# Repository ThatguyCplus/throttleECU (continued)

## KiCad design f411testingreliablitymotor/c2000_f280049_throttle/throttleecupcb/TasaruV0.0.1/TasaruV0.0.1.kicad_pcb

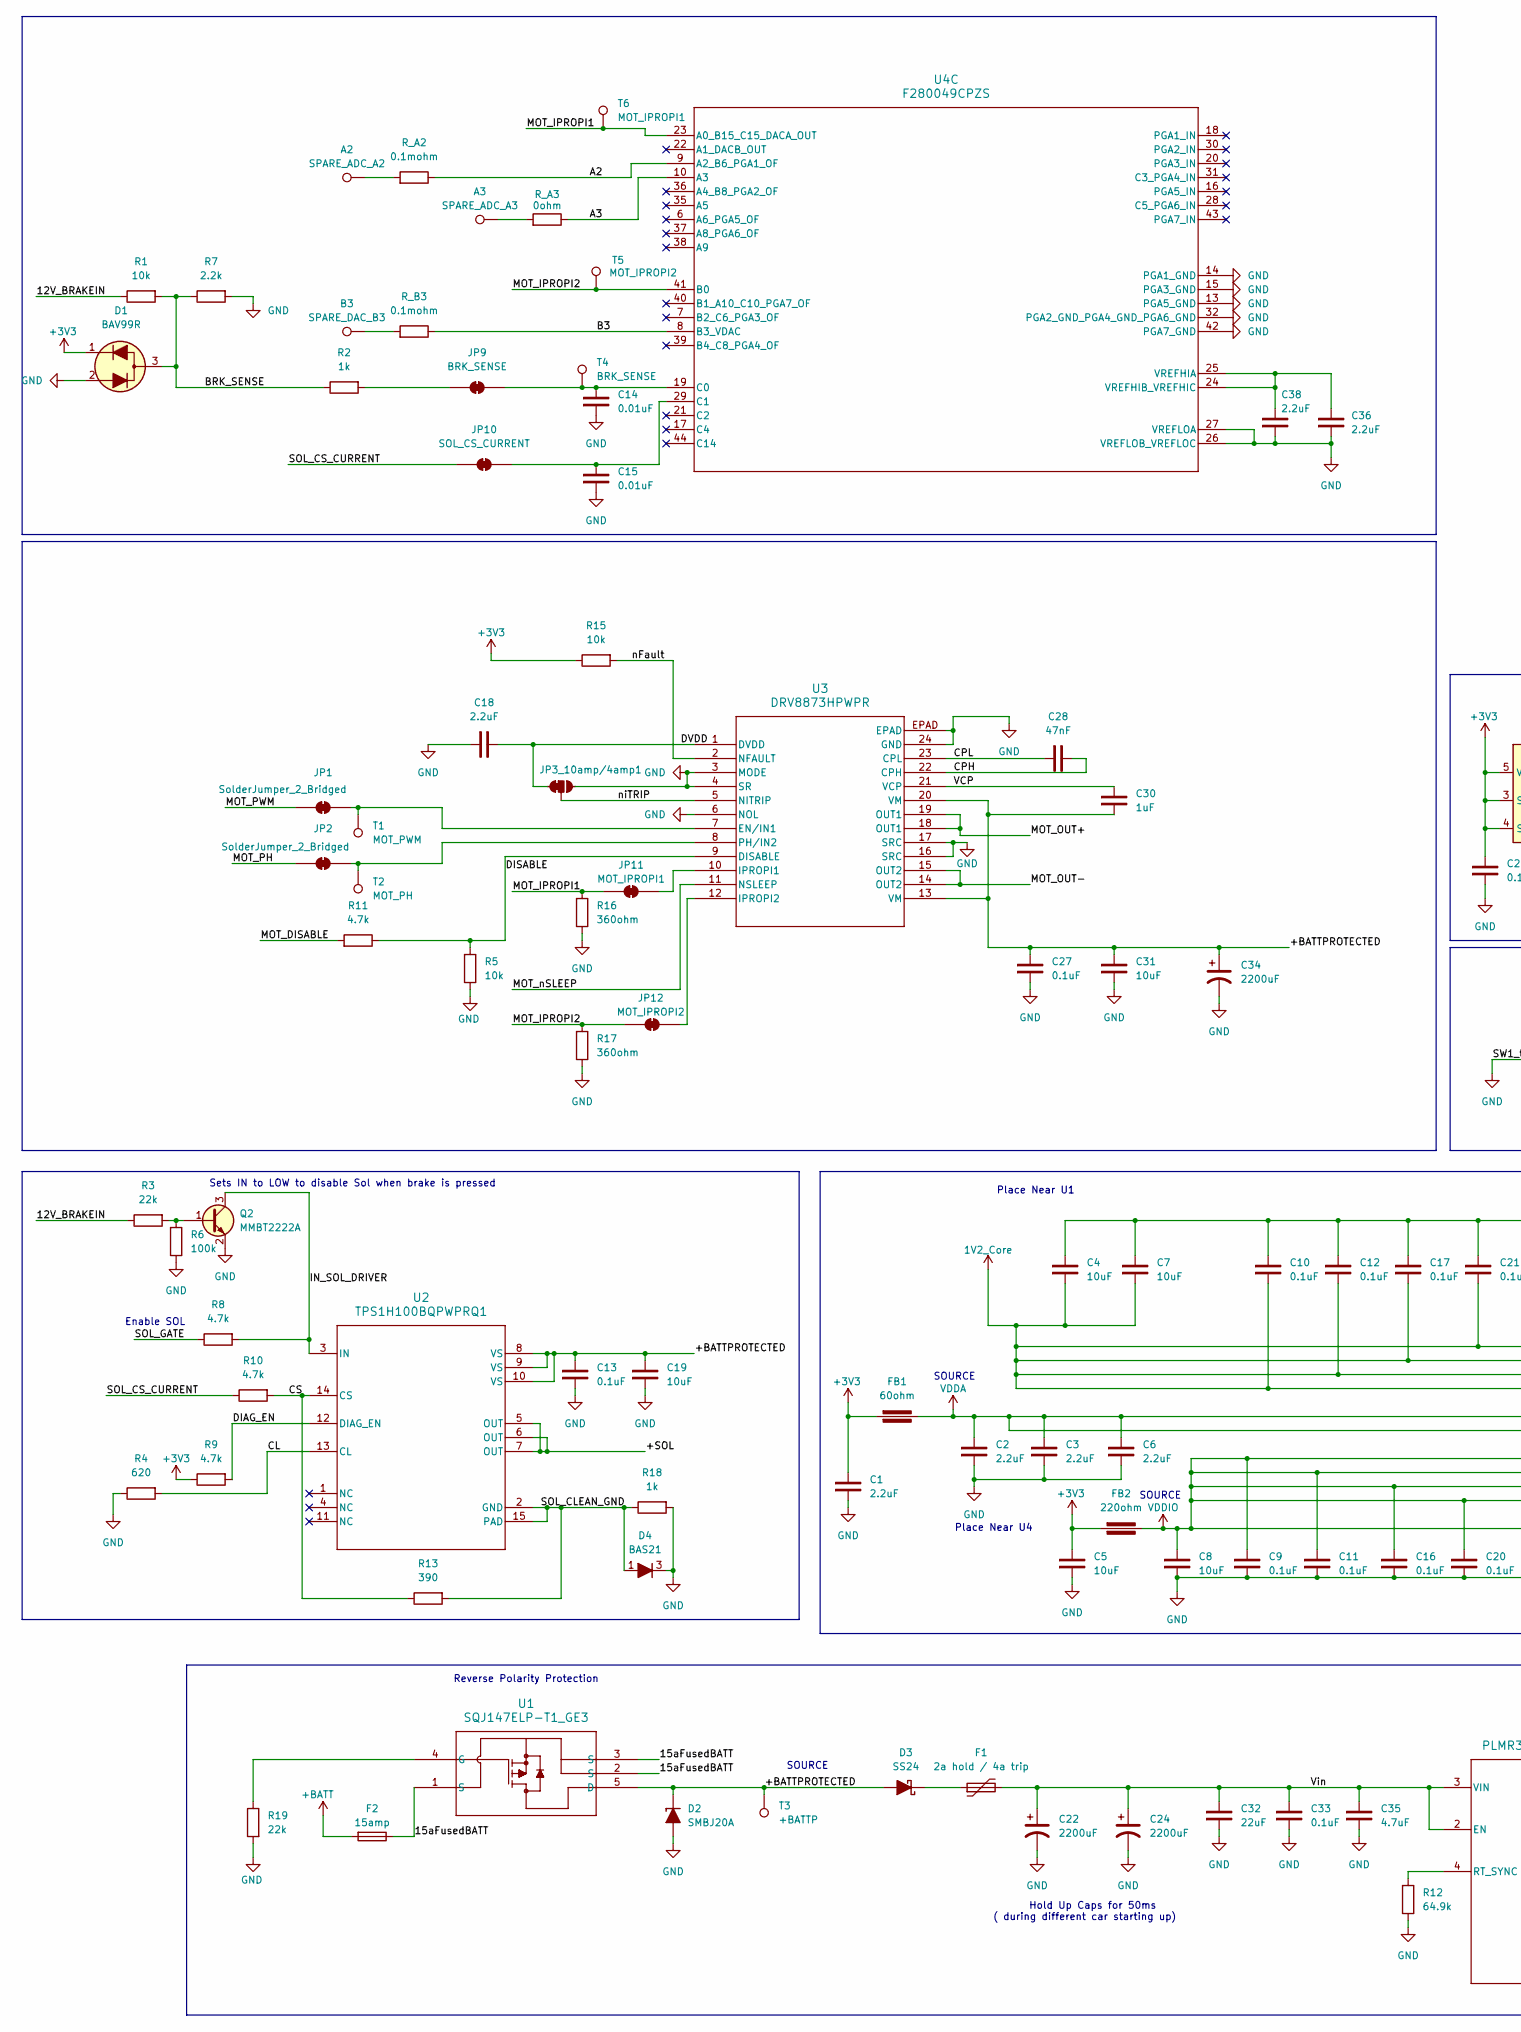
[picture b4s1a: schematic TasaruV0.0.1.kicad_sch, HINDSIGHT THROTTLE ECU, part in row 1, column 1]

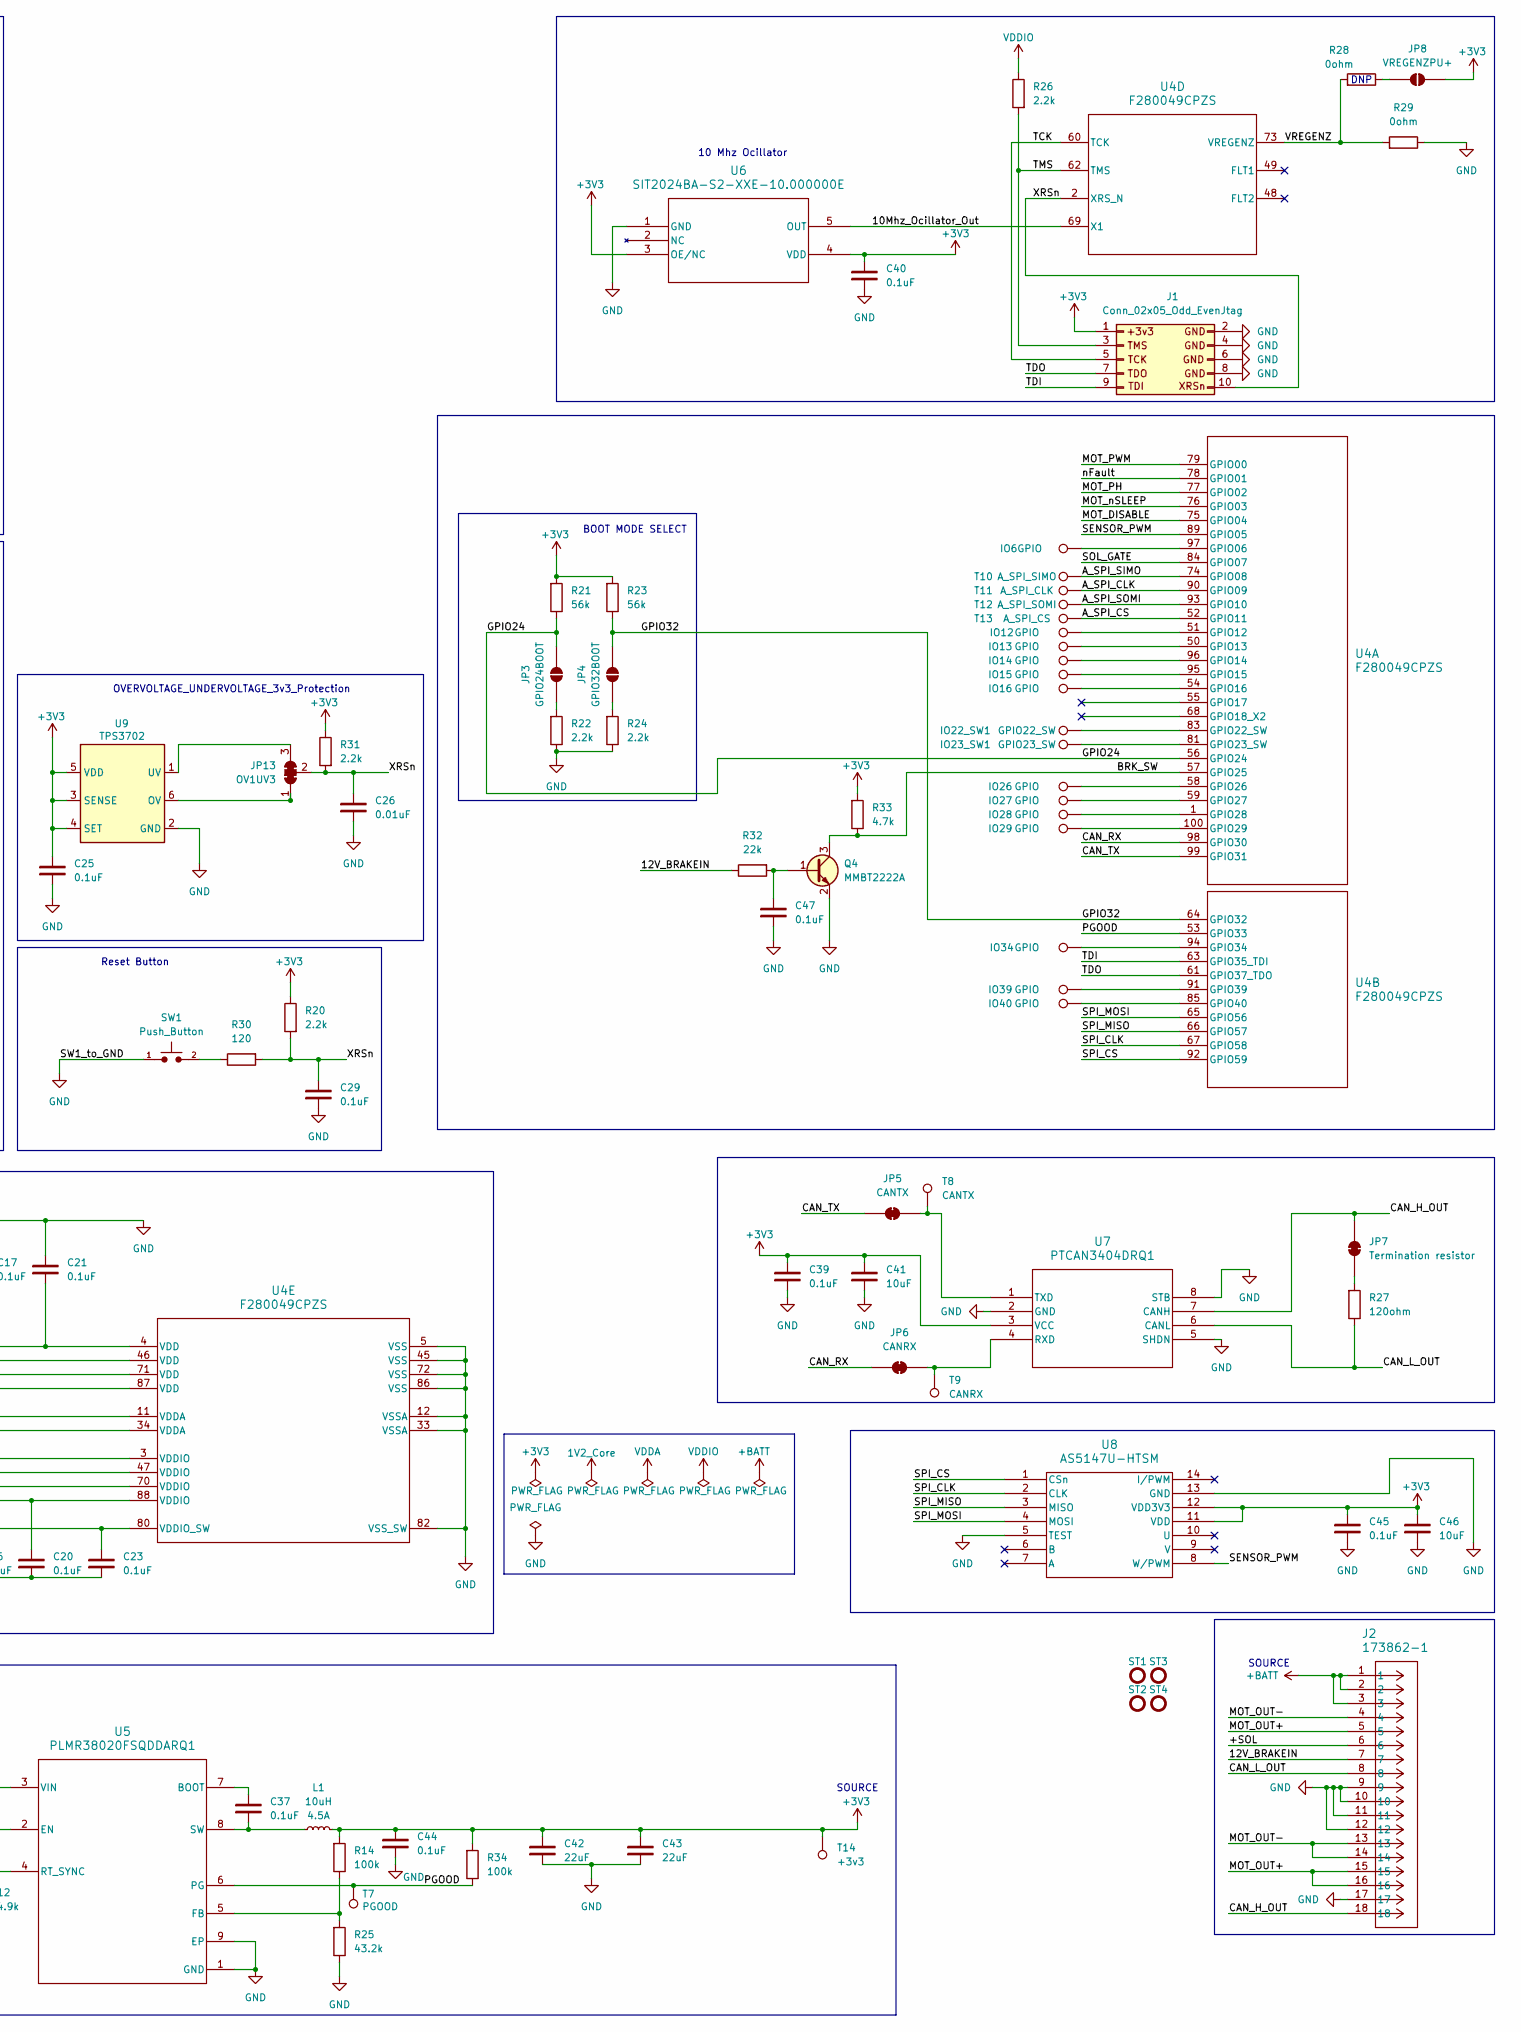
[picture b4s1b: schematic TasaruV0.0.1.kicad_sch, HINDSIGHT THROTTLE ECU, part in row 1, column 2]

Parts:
A2: SPARE_ADC_A2; TestPoint_Pad_D1.5mm
A3: SPARE_ADC_A3; TestPoint_Pad_D1.5mm
B3: SPARE_DAC_B3; TestPoint_Pad_D1.5mm
C1, C2, C3, C6, C18, C36, C38: 2.2uF; C_0603_1608Metric_Pad1.08x0.95mm_HandSolder
C4, C5, C7, C8, C19, C31, C41, C46: 10uF; C_0805_2012Metric_Pad1.18x1.45mm_HandSolder
C9, C10, C11, C12, C13, C16, C17, C20, C21, C23, C25, C27, C29, C37, C39, C40, C44, C45, C47: 0.1uF; C_0603_1608Metric_Pad1.08x0.95mm_HandSolder
C14, C15, C26: 0.01uF; C_0603_1608Metric_Pad1.08x0.95mm_HandSolder
C22, C24, C34: 2200uF; CP_Radial_D12.5mm_P5.00mm
C28: 47nF; C_0603_1608Metric_Pad1.08x0.95mm_HandSolder
C30: 1uF; C_0603_1608Metric_Pad1.08x0.95mm_HandSolder
C32, C42, C43: 22uF; C_1206_3216Metric_Pad1.33x1.80mm_HandSolder
C33: 0.1uF; C_1206_3216Metric_Pad1.33x1.80mm_HandSolder
C35: 4.7uF; C_0603_1608Metric_Pad1.08x0.95mm_HandSolder
D1: BAV99R; SOT-23
D2: SMBJ20A; D_SMB_TVS
D3: SS24; D_SMB
D4: BAS21; SOT-23_Handsoldering
F1: 2a hold / 4a trip; Fuse_1812_4532Metric_Pad1.30x3.40mm_HandSolder
F2: 15amp; Fuseholder_Blade_Mini_Keystone_3568
FB1: 60ohm; Fuse_0603_1608Metric_Pad1.05x0.95mm_HandSolder
FB2: 220ohm; Fuse_0603_1608Metric_Pad1.05x0.95mm_HandSolder
IO6, IO12, IO13, IO14, IO15, IO16, IO26, IO27, IO28, IO29, IO34, IO39, IO40: GPIO; TestPoint_Pad_D1.0mm
IO22_SW1: GPIO22_SW; TestPoint_Pad_D1.0mm
IO23_SW1: GPIO23_SW; TestPoint_Pad_D1.0mm
J1: Conn_02x05_Odd_EvenJtag; IDC-Header_2x05_P2.54mm_Vertical
J2: 173862-1; CONN_173862-1_TYC
JP1, JP2: SolderJumper_2_Bridged; SolderJumper-2_P1.3mm_Bridged2Bar_RoundedPad1.0x1.5mm
JP3: GPIO24BOOT; SolderJumper-2_P1.3mm_Open_RoundedPad1.0x1.5mm
JP3_10amp/4amp1: SolderJumper-3_P1.3mm_Bridged12_RoundedPad1.0x1.5mm_NumberL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
JP4: GPIO32BOOT; SolderJumper-2_P1.3mm_Open_RoundedPad1.0x1.5mm
JP5: CANTX; SolderJumper-2_P1.3mm_Bridged2Bar_RoundedPad1.0x1.5mm
JP6: CANRX; SolderJumper-2_P1.3mm_Bridged2Bar_RoundedPad1.0x1.5mm
JP7: Termination resistor; SolderJumper-2_P1.3mm_Bridged2Bar_RoundedPad1.0x1.5mm
JP8: VREGENZPU+; SolderJumper-2_P1.3mm_Open_RoundedPad1.0x1.5mm
JP9: BRK_SENSE; SolderJumper-2_P1.3mm_Bridged2Bar_RoundedPad1.0x1.5mm
JP10: SOL_CS_CURRENT; SolderJumper-2_P1.3mm_Bridged2Bar_RoundedPad1.0x1.5mm
JP11: MOT_IPROPI1; SolderJumper-2_P1.3mm_Bridged2Bar_RoundedPad1.0x1.5mm
JP12: MOT_IPROPI2; SolderJumper-2_P1.3mm_Bridged2Bar_RoundedPad1.0x1.5mm
JP13: OV1UV3; SolderJumper-3_P1.3mm_Bridged123_RoundedPad1.0x1.5mm_Number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
L1: 10uH; Inductor_7.3x6.6mm
Q2, Q4: MMBT2222A; SOT-23
R1, R5, R15: 10k; R_0402_1005Metric_Pad0.72x0.64mm_HandSolder
R2, R18: 1k; R_0402_1005Metric_Pad0.72x0.64mm_HandSolder
R3, R32: 22k; R_0402_1005Metric_Pad0.72x0.64mm_HandSolder
R4: 620; R_0402_1005Metric_Pad0.72x0.64mm_HandSolder
R6, R14: 100k; R_0402_1005Metric_Pad0.72x0.64mm_HandSolder
R7, R20, R22, R24, R26, R31: 2.2k; R_0402_1005Metric_Pad0.72x0.64mm_HandSolder
R8, R9, R10, R11, R33: 4.7k; R_0402_1005Metric_Pad0.72x0.64mm_HandSolder
R12: 64.9k; R_0402_1005Metric_Pad0.72x0.64mm_HandSolder
R13: 390; R_0402_1005Metric_Pad0.72x0.64mm_HandSolder
R16, R17: 360ohm; R_0603_1608Metric_Pad0.98x0.95mm_HandSolder
R19: 22k; R_0603_1608Metric_Pad0.98x0.95mm_HandSolder
R21, R23: 56k; R_0402_1005Metric_Pad0.72x0.64mm_HandSolder
R25: 43.2k; R_0603_1608Metric_Pad0.98x0.95mm_HandSolder
R27: 120ohm; R_0603_1608Metric_Pad0.98x0.95mm_HandSolder
R28, R29: 0ohm; R_0402_1005Metric_Pad0.72x0.64mm_HandSolder
R30: 120; R_0603_1608Metric_Pad0.98x0.95mm_HandSolder
R34: 100k; R_0603_1608Metric_Pad0.98x0.95mm_HandSolder
R_A2: 0.1mohm; R_0402_1005Metric_Pad0.72x0.64mm_HandSolder
R_A3: 0ohm; R_0402_1005Metric_Pad0.72x0.64mm_HandSolder
R_B3: 0.1mohm; R_0402_1005Metric_Pad0.72x0.64mm_HandSolder
ST1, ST2, ST3, ST4: FASTNER; Standoff_Hole-2.75mm_Clearance-1.625mm
SW1: Push_Button; SW_PUSH_6mm_H5mm
T1: MOT_PWM; TestPoint_Pad_D1.0mm
T2: MOT_PH; TestPoint_Pad_D1.0mm
T3: +BATTP; TestPoint_Pad_D1.0mm
T4: BRK_SENSE; TestPoint_Pad_D1.0mm
T5: MOT_IPROPI2; TestPoint_Pad_D1.0mm
T6: MOT_IPROPI1; TestPoint_Pad_D1.0mm
T7: PGOOD; TestPoint_Pad_D1.0mm
T8: CANTX; TestPoint_Pad_D1.0mm
T9: CANRX; TestPoint_Pad_D1.0mm
T10: A_SPI_SIMO; TestPoint_Pad_D1.0mm
T11: A_SPI_CLK; TestPoint_Pad_D1.0mm
T12: A_SPI_SOMI; TestPoint_Pad_D1.0mm
T13: A_SPI_CS; TestPoint_Pad_D1.0mm
T14: +3v3; TestPoint_Pad_D1.0mm
U1: SQJ147ELP-T1_GE3; PowerPAK_SO-8L_3_VIS
U2: TPS1H100BQPWPRQ1; PWP0014F_M
U3: DRV8873HPWPR; PWP24_TEX-M
U4: F280049CPZS; PZ0100A_M
U5: PLMR38020FSQDDARQ1; DDA0008E-IPC_A
U6: SIT2024BA-S2-XXE-10.000000E; SOT_SiT1630-S_SIT
U7: PTCAN3404DRQ1; SOIC8_D_TEX-M
U8: AS5147U-HTSM; TSSOP14_AMS-M
U9: TPS3702; SOT-23-6_Handsoldering

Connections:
1V2_Core: C4.1, C7.1, C10.1, C12.1, C17.1, C21.1, U4.4 (VDD), U4.46 (VDD), U4.71 (VDD), U4.87 (VDD)
+3V3: C1.2, C5.2, C25.2, C39.2, C40.2, C41.2, C42.2, C43.2, C44.2, C45.2, C46.2, D1.1 (A), FB1.1, FB2.1, J1.1, JP8.2 (B), L1.2, R9.2, R14.1, R15.2, R20.2, R21.1, R23.1, R31.2, R33.1, R34.1, T14.1 (1_1), U6.3 (OE/NC), U6.4 (VDD), U7.3 (VCC), U8.11 (VDD), U8.12 (VDD3V3), U9.3 (SENSE), U9.4 (SET), U9.5 (VDD)
+BATT: F2.2, J2.1, J2.2, J2.3
/10Mhz_Ocillator_Out: U4.69 (X1), U6.5 (OUT)
/12V_BRAKEIN: J2.7, R1.2, R3.2, R32.2
/15aFusedBATT: F2.1, U1.1 (S), U1.2 (S), U1.3 (S)
/+BATTPROTECTED: C13.2, C19.2, C27.2, C30.1, C31.2, C34.1, D2.1 (K), D3.2 (A), T3.1 (1_1), U1.5 (D), U2.8 (VS), U2.9 (VS), U2.10 (VS), U3.13 (VM), U3.20 (VM)
/+SOL: J2.6, U2.5 (OUT), U2.6 (OUT), U2.7 (OUT)
/A2: R_A2.2, U4.9 (A2_B6_PGA1_OF)
/A3: R_A3.2, U4.10 (A3)
/A_SPI_CLK: T11.1 (1_1), U4.90 (GPIO09)
/A_SPI_CS: T13.1 (1_1), U4.52 (GPIO11)
/A_SPI_SIMO: T10.1 (1_1), U4.74 (GPIO08)
/A_SPI_SOMI: T12.1 (1_1), U4.93 (GPIO10)
/B3: R_B3.2, U4.8 (B3_VDAC)
/BRK_SENSE: D1.3 (C), R1.1, R2.2, R7.2
/BRK_SW: Q4.3 (C), R33.2, U4.57 (GPIO25)
/CAN_H_OUT: J2.18, JP7.2 (B), U7.7 (CANH)
/CAN_L_OUT: J2.8, R27.2, U7.6 (CANL)
/CAN_RX: JP6.1 (A), U4.98 (GPIO30)
/CAN_TX: JP5.1 (A), U4.99 (GPIO31)
/CL: R4.1, U2.13 (CL)
/CPH: C28.2, U3.22 (CPH)
/CPL: C28.1, U3.23 (CPL)
/CS: R10.1, R13.2, U2.14 (CS)
/DIAG_EN: R9.1, U2.12 (DIAG_EN)
/DISABLE: R5.1, R11.2, U3.9 (DISABLE)
/DVDD: C18.2, JP3_10amp/4amp1.1 (A), U3.1 (DVDD)
/GPIO24: JP3.2 (B), R21.2, U4.56 (GPIO24)
/GPIO32: JP4.2 (B), R23.2, U4.64 (GPIO32)
/IN_SOL_DRIVER: Q2.3 (C), R8.1, U2.3 (IN)
/MOT_DISABLE: R11.1, U4.75 (GPIO04)
/MOT_IPROPI1: JP11.1 (A), R16.1, T6.1 (1_1), U4.23 (A0_B15_C15_DACA_OUT)
/MOT_IPROPI2: JP12.1 (A), R17.1, T5.1 (1_1), U4.41 (B0)
/MOT_OUT+: J2.5, J2.15, J2.16, U3.18 (OUT1), U3.19 (OUT1)
/MOT_OUT-: J2.4, J2.13, J2.14, U3.14 (OUT2), U3.15 (OUT2)
/MOT_PH: JP2.1 (A), U4.77 (GPIO02)
/MOT_PWM: JP1.1 (A), U4.79 (GPIO00)
/MOT_nSLEEP: U3.11 (NSLEEP), U4.76 (GPIO03)
/PGOOD: R34.2, T7.1 (1_1), U4.53 (GPIO33), U5.6 (PG)
/SENSOR_PWM: U4.89 (GPIO05), U8.8 (W/PWM)
/SOL_CLEAN_GND: D4.1 (A), R13.1, R18.2, U2.2 (GND), U2.15 (PAD)
/SOL_CS_CURRENT: JP10.1 (A), R10.2
/SOL_GATE: R8.2, U4.84 (GPIO07)
/SPI_CLK: U4.67 (GPIO58), U8.2 (CLK)
/SPI_CS: U4.92 (GPIO59), U8.1 (CSn)
/SPI_MISO: U4.66 (GPIO57), U8.3 (MISO)
/SPI_MOSI: U4.65 (GPIO56), U8.4 (MOSI)
/TCK: J1.5, U4.60 (TCK)
/TDI: J1.9, U4.63 (GPIO35_TDI)
/TDO: J1.7, U4.61 (GPIO37_TDO)
/TMS: J1.3, R26.1, U4.62 (TMS)
/VCP: C30.2, U3.21 (VCP)
/VREGENZ: R28.1, R29.1, U4.73 (VREGENZ)
/Vin: C22.1, C24.1, C32.2, C33.2, C35.2, F1.2, U5.2 (EN), U5.3 (VIN)
/XRSn: C26.2, C29.2, J1.10, JP13.2 (C), R20.1, R30.1, R31.1, U4.2 (XRS_N)
/nFault: R15.1, U3.2 (NFAULT), U4.78 (GPIO01)
/niTRIP: JP3_10amp/4amp1.2 (B), U3.5 (NITRIP)
GND: C1.1, C2.1, C3.1, C4.2, C5.1, C6.1, C7.2, C8.1, C9.1, C10.2, C11.1, C12.2, C13.1, C14.1, C15.1, C16.1, C17.2, C18.1, C19.1, C20.1, C21.2, C22.2, C23.1, C24.2, C25.1, C26.1, C27.1, C29.1, C31.1, C32.1, C33.1, C34.2, C35.1, C36.1, C38.1, C39.1, C40.1, C41.1, C42.1, C43.1, C44.1, C45.1, C46.1, C47.1, D1.2 (K), D2.2 (A), D4.3 (K), J1.2, J1.4, J1.6, J1.8, J2.9, J2.10, J2.11, J2.12, J2.17, JP3_10amp/4amp1.3 (C), Q2.2 (E), Q4.2 (E), R4.2, R5.2, R6.2, R7.1, R12.2, R16.2, R17.2, R18.1, R19.1, R22.2, R24.2, R25.2, R29.2, SW1.1, U3.3 (MODE), U3.4 (SR), U3.6 (NOL), U3.16 (SRC), U3.17 (SRC), U3.24 (GND), U3.EPAD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
unnamed: A2.1 (1_1), R_A2.1
unnamed: A3.1 (1_1), R_A3.1
unnamed: B3.1 (1_1), R_B3.1
unnamed: D3.1 (K), F1.1
unnamed: JP1.2 (B), T1.1 (1_1), U3.7 (EN/IN1)
unnamed: JP2.2 (B), T2.1 (1_1), U3.8 (PH/IN2)
unnamed: JP3.1 (A), R22.1
unnamed: JP4.1 (A), R24.1
unnamed: JP5.2 (B), T8.1 (1_1), U7.1 (TXD)
unnamed: JP6.2 (B), T9.1 (1_1), U7.4 (RXD)
unnamed: JP7.1 (A), R27.1
unnamed: JP8.1 (A), R28.2
unnamed: JP9.1 (A), R2.1
unnamed: C14.2, JP9.2 (B), T4.1 (1_1), U4.19 (C0)
unnamed: C15.2, JP10.2 (B), U4.29 (C1)
unnamed: JP11.2 (B), U3.10 (IPROPI1)
unnamed: JP12.2 (B), U3.12 (IPROPI2)
unnamed: JP13.1 (A), U9.6 (OV)
unnamed: JP13.3 (B), U9.1 (UV)
unnamed: Q2.1 (B), R3.1, R6.1
unnamed: C47.2, Q4.1 (B), R32.1
unnamed: R30.2, SW1.2
unnamed: R19.2, U1.4 (G)
unnamed: IO6.1 (1_1), U4.97 (GPIO06)
unnamed: IO12.1 (1_1), U4.51 (GPIO12)
unnamed: IO13.1 (1_1), U4.50 (GPIO13)
unnamed: IO14.1 (1_1), U4.96 (GPIO14)
unnamed: IO15.1 (1_1), U4.95 (GPIO15)
unnamed: IO16.1 (1_1), U4.54 (GPIO16)
unnamed: IO22_SW1.1 (1_1), U4.83 (GPIO22_SW)
unnamed: IO23_SW1.1 (1_1), U4.81 (GPIO23_SW)
unnamed: IO26.1 (1_1), U4.58 (GPIO26)
unnamed: IO27.1 (1_1), U4.59 (GPIO27)
unnamed: IO28.1 (1_1), U4.1 (GPIO28)
unnamed: IO29.1 (1_1), U4.100 (GPIO29)
unnamed: IO34.1 (1_1), U4.94 (GPIO34)
unnamed: IO39.1 (1_1), U4.91 (GPIO39)
unnamed: IO40.1 (1_1), U4.85 (GPIO40)
unnamed: C36.2, C38.2, U4.24 (VREFHIB_VREFHIC), U4.25 (VREFHIA)
unnamed: C37.2, U5.7 (BOOT)
unnamed: R14.2, R25.1, U5.5 (FB)
unnamed: R12.1, U5.4 (RT_SYNC)
unnamed: C37.1, L1.1, U5.8 (SW)
VDDA: C2.2, C3.2, C6.2, FB1.2, U4.11 (VDDA), U4.34 (VDDA)
VDDIO: C8.2, C9.2, C11.2, C16.2, C20.2, C23.2, FB2.2, R26.2, U4.3 (VDDIO), U4.47 (VDDIO), U4.70 (VDDIO), U4.80 (VDDIO_SW), U4.88 (VDDIO)

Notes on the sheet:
SOURCE
10 Mhz Ocillator
Sets IN to LOW to disable Sol when brake is pressed
DNP
Reverse Polarity Protection
BOOT MODE SELECT
OVERVOLTAGE_UNDERVOLTAGE_3v3_Protection
Hold Up Caps for 50ms ( during different car starting up)
Reset Button
Place Near U4
Enable SOL
Place Near U1

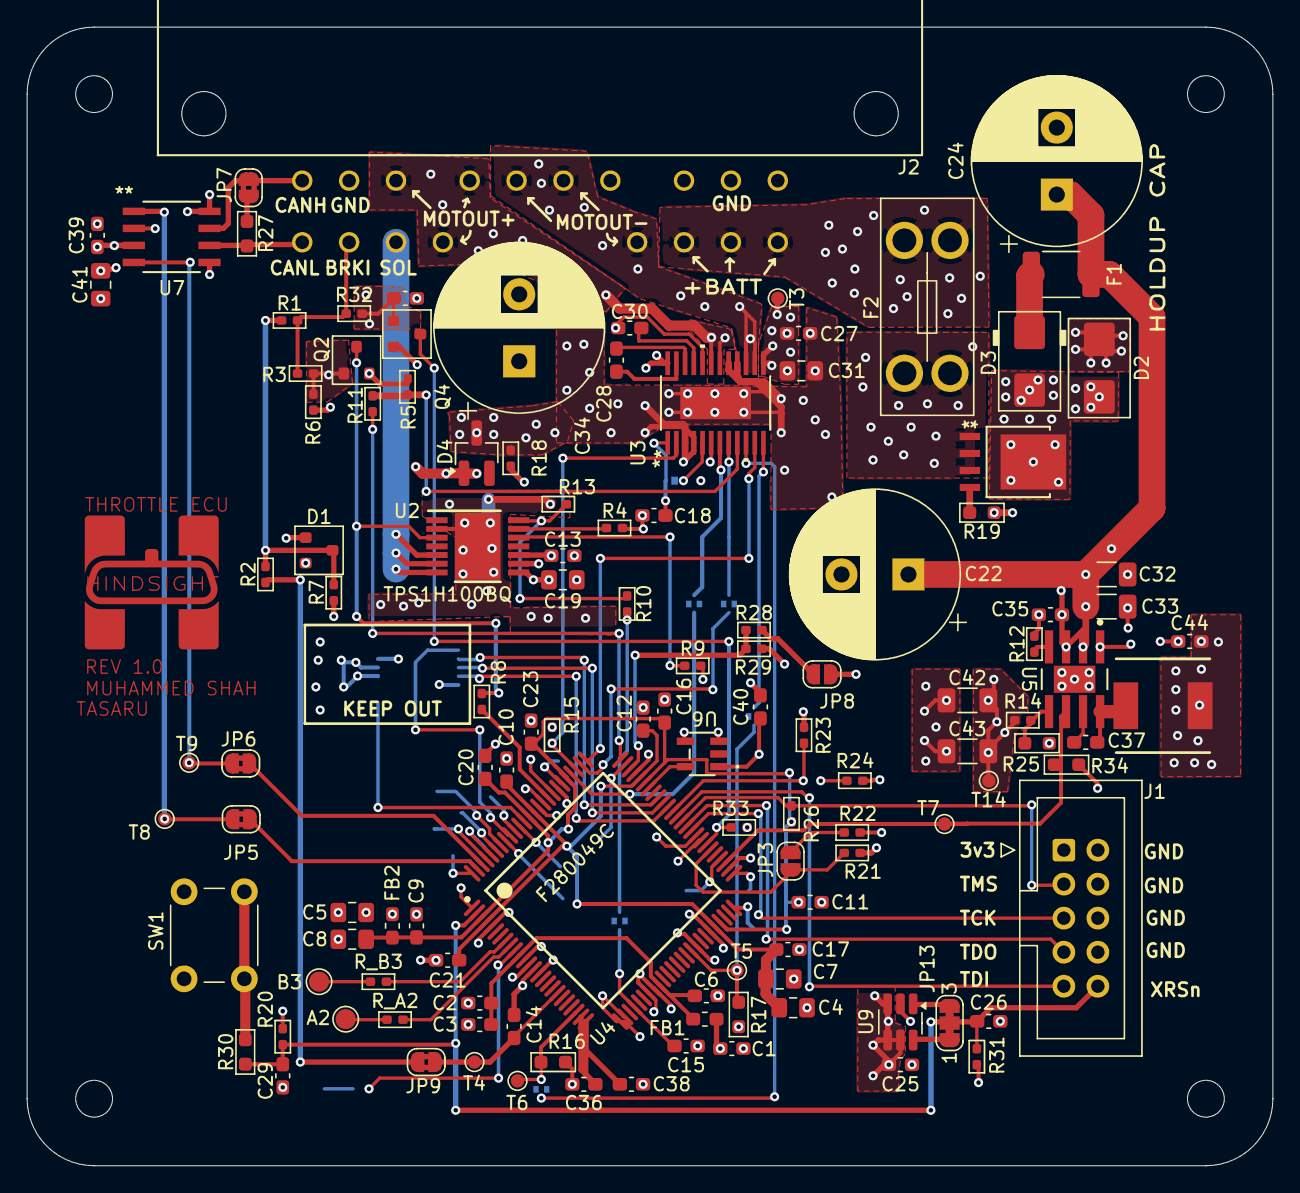
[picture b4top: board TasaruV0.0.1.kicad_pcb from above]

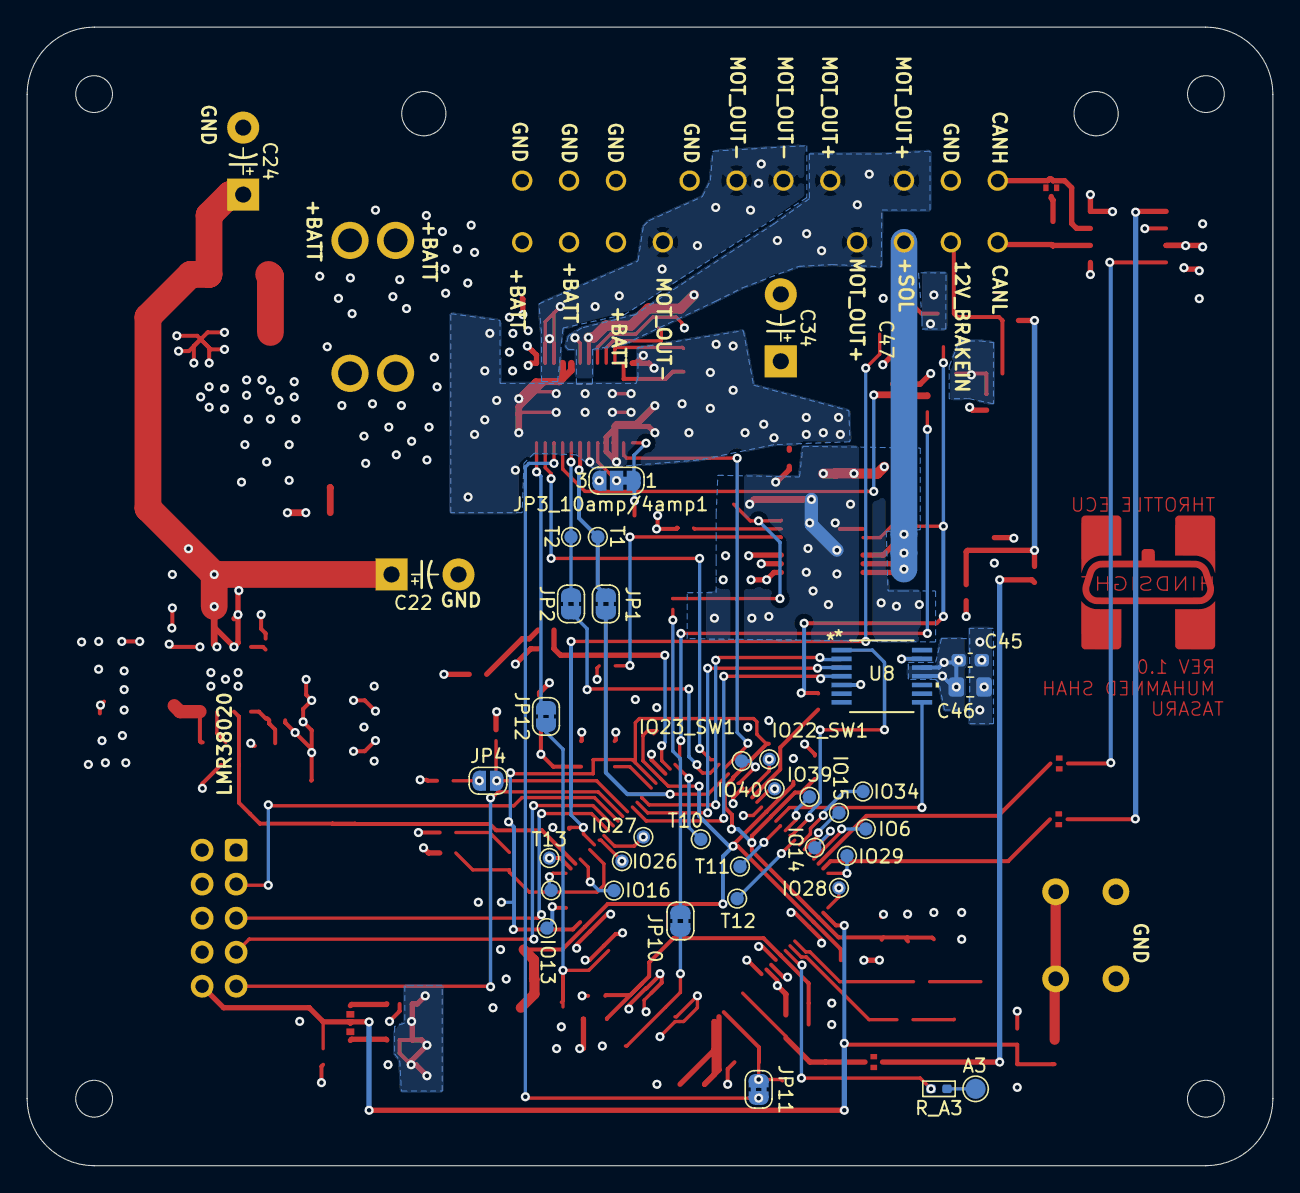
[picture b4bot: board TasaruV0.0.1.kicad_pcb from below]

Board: 4 copper layers, 93.0 x 85.0 mm, 158 parts (33 on the bottom side), 104 nets.

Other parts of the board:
HINDSIGHT: LOGO; hindsight_logo_gold

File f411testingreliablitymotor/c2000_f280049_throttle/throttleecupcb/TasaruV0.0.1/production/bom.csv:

Designator,Footprint,Quantity,Value,LCSC Part #
A2,TestPoint_Pad_D1.5mm,1,SPARE_ADC_A2,
A3,TestPoint_Pad_D1.5mm,1,SPARE_ADC_A3,
B3,TestPoint_Pad_D1.5mm,1,SPARE_DAC_B3,
"C1, C18, C2, C3, C36, C38, C6",0603,7,2.2uF,
"C10, C11, C12, C13, C16, C17, C20, C21, C23, C25, C27, C29, C37, C39, C40, C44, C45, C47, C9",0603,19,0.1uF,
"C14, C15, C26",0603,3,0.01uF,
"C19, C31, C4, C41, C46, C5, C7, C8",0805,8,10uF,
"C22, C24, C34",CP_Radial_D12.5mm_P5.00mm,3,2200uF,
C28,0603,1,47nF,
C30,0603,1,1uF,
"C32, C42, C43",1206,3,22uF,
C33,1206,1,0.1uF,
C35,0603,1,4.7uF,
D1,SOT-23,1,BAV99,
D2,D_SMB_TVS,1,SMBJ20A,
D3,D_SMB,1,SS24,
D4,SOT-23_Handsoldering,1,BAS21,
F1,1812,1,2a hold / 4a trip,
F2,Fuseholder_Blade_Mini_Keystone_3568,1,15amp,
FB1,0603,1,60ohm,
FB2,0603,1,220ohm,
"IO12, IO13, IO14, IO15, IO16, IO26, IO27, IO28, IO29, IO34, IO39, IO40, IO6",TestPoint_Pad_D1.0mm,13,GPIO,
IO22_SW1,TestPoint_Pad_D1.0mm,1,GPIO22_SW,
IO23_SW1,TestPoint_Pad_D1.0mm,1,GPIO23_SW,
J1,IDC-Header_2x05_P2.54mm_Vertical,1,Conn_02x05_Odd_EvenJtag,
J2,CONN_173862-1_TYC,1,173862-1,
JP3_10AMP/4AMP1,SolderJumper-3_P1.3mm_Bridged12_RoundedPad1.0x1.5mm_NumberLabels,1,~,
L1,Inductor_7.3x6.6mm,1,10uH,
"Q2, Q4",SOT-23,2,MMBT2222A,
"R1, R15, R5",0402,3,10k,
"R10, R11, R33, R8, R9",0402,5,4.7k,
R12,0402,1,64.9k,
R13,0402,1,390,
"R14, R6",0402,2,100k,
"R16, R17",0603,2,360ohm,
"R18, R2",0402,2,1k,
R19,0603,1,22k,
"R20, R22, R24, R26, R31, R7",0402,6,2.2k,
"R21, R23",0402,2,56k,
R25,0603,1,43.2k,
R27,0603,1,120ohm,
"R28, R29, R_A3",0402,3,0ohm,
"R3, R32",0402,2,22k,
R30,0603,1,120,
R34,0603,1,100k,
R4,0402,1,620,
"R_A2, R_B3",0402,2,0.1mohm,
SW1,SW_PUSH_6mm_H5mm,1,Push_Button,
T1,TestPoint_Pad_D1.0mm,1,MOT_PWM,
T10,TestPoint_Pad_D1.0mm,1,A_SPI_SIMO,
T11,TestPoint_Pad_D1.0mm,1,A_SPI_CLK,
T12,TestPoint_Pad_D1.0mm,1,A_SPI_SOMI,
T13,TestPoint_Pad_D1.0mm,1,A_SPI_CS,
T14,TestPoint_Pad_D1.0mm,1,+3v3,
T2,TestPoint_Pad_D1.0mm,1,MOT_PH,
T3,TestPoint_Pad_D1.0mm,1,+BATTP,
T4,TestPoint_Pad_D1.0mm,1,BRK_SENSE,
T5,TestPoint_Pad_D1.0mm,1,MOT_IPROPI2,
T6,TestPoint_Pad_D1.0mm,1,MOT_IPROPI1,
T7,TestPoint_Pad_D1.0mm,1,PGOOD,
T8,TestPoint_Pad_D1.0mm,1,CANTX,
T9,TestPoint_Pad_D1.0mm,1,CANRX,
U1,PowerPAK_SO-8L_3_VIS,1,SQJ147ELP-T1_GE3,
U2,PWP0014F_M,1,TPS1H100BQPWPRQ1,
U3,PWP24_TEX-M,1,DRV8873HPWPR,
U4,PZ0100A_M,1,F280049CPZS,
U5,DDA0008E-IPC_A,1,PLMR38020FSQDDARQ1,
U6,SOT_SiT1630-S_SIT,1,SIT2024BA-S2-XXE-10.000000E,
U7,SOIC8_D_TEX-M,1,PTCAN3404DRQ1,
U8,TSSOP14_AMS-M,1,AS5147U-HTSM,
U9,SOT-23-6_Handsoldering,1,TPS3702,

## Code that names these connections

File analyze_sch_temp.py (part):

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
pin_defs = {
    1: [
        ('1','GPIO28',-17.78,-27.94,0,5.08),('50','GPIO13',-17.78,2.54,0,5.08),
        ('51','GPIO12',-17.78,5.08,0,5.08),('52','GPIO11',-17.78,7.62,0,5.08),
        ('54','GPIO16',-17.78,-5.08,0,5.08),('55','GPIO17',-17.78,-7.62,0,5.08),
        ('56','GPIO24',-17.78,-17.78,0,5.08),('57','GPIO25',-17.78,-20.32,0,5.08),
        ('58','GPIO26',-17.78,-22.86,0,5.08),('59','GPIO27',-17.78,-25.4,0,5.08),
        ('68','GPIO18_X2',-17.78,-10.16,0,5.08),('74','GPIO08',-17.78,15.24,0,5.08),
        ('75','GPIO04',-17.78,25.4,0,5.08),('76','GPIO03',-17.78,27.94,0,5.08),
        ('77','GPIO02',-17.78,30.48,0,5.08),('78','GPIO01',-17.78,33.02,0,5.08),
        ('79','GPIO00',-17.78,35.56,0,5.08),('81','GPIO23_SW',-17.78,-15.24,0,5.08),
        ('83','GPIO22_SW',-17.78,-12.7,0,5.08),('84','GPIO07',-17.78,17.78,0,5.08),
        ('89','GPIO05',-17.78,22.86,0,5.08),('90','GPIO09',-17.78,12.7,0,5.08),
        ('93','GPIO10',-17.78,10.16,0,5.08),('95','GPIO15',-17.78,-2.54,0,5.08),
        ('96','GPIO14',-17.78,0,0,5.08),('97','GPIO06',-17.78,20.32,0,5.08),
        ('98','GPIO30',-17.78,-33.02,0,5.08),('99','GPIO31',-17.78,-35.56,0,5.08),
        ('100','GPIO29',-17.78,-30.48,0,5.08),
    ],
    2: [
        ('53','GPIO33',-17.78,10.16,0,5.08),('61','GPIO37_TDO',-17.78,2.54,0,5.08),
        ('63','GPIO35_TDI',-17.78,5.08,0,5.08),('64','GPIO32',-17.78,12.7,0,5.08),
        ('65','GPIO56',-17.78,-5.08,0,5.08),('66','GPIO57',-17.78,-7.62,0,5.08),
        ('67','GPIO58',-17.78,-10.16,0,5.08),('85','GPIO40',-17.78,-2.54,0,5.08),
        ('91','GPIO39',-17.78,0,0,5.08),('92','GPIO59',-17.78,-12.7,0,5.08),
        ('94','GPIO34',-17.78,7.62,0,5.08),
    ],
    3: [
        ('6','A6_PGA5_OF',-50.8,12.7,0,5.08),('7','B2_C6_PGA3_OF',-50.8,-5.08,0,5.08),
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
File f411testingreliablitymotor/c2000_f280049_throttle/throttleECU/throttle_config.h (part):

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#define CFG_MOT_DISABLE_PIN_CONFIG GPIO_4_GPIO4
#define CFG_MOT_DISABLE_PIN        4U

/* DRV8873H nFAULT — GPIO1 (pkg-pin 78), open-drain active-LOW, pulled up via R15 (10k → 3V3)
 * LOW = fault (OCP, OTW, OTS, UVLO). HIGH = normal. */
#define CFG_MOT_NFAULT_PIN_CONFIG  GPIO_1_GPIO1
#define CFG_MOT_NFAULT_PIN         1U
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#define CFG_RELAY_PIN_CONFIG GPIO_7_GPIO7

/* Encoder: AS5147U via bit-bang SPI
 *   MOSI  GPIO56  pkg-pin 65  (MCU → sensor, commands/NOP)
 *   MISO  GPIO57  pkg-pin 66  (sensor → MCU, angle data)
 *   CLK   GPIO58  pkg-pin 67  (SPI clock, idle LOW)
 *   CS    GPIO59  pkg-pin 92  (chip-select, active LOW)
 *
 *   Note: schematic incorrectly listed GPIO40/56/57 — corrected to actual
 *   package pin → GPIO mapping from C2000Ware LAUNCHXL_F280049C.syscfg.json.
 *   W/PWM output (SENSOR_PWM net, GPIO5) is not used — SPI is primary.
 */
#define CFG_ENC_SPI_MOSI_PIN     56U
#define CFG_ENC_SPI_MOSI_CONFIG  GPIO_56_GPIO56
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/* IPROPI2: pin 41 = ADCB_IN0 (schematic B0), internal VREF (VREFHIB not on PCB) */
#define CFG_ADC_LIS_SOC      ADC_SOC_NUMBER0
#define CFG_ADC_LIS_CH       ADC_CH_ADCIN0
/* SOL_CS_CURRENT: pin 29 = ADCC_IN1 (schematic C1), via JP10, internal VREF */
#define CFG_ADC_SOL_SOC      ADC_SOC_NUMBER0
#define CFG_ADC_SOL_CH       ADC_CH_ADCIN1
/* BRK_SENSE: pin 19 = ADCC_IN0 (schematic C0), 12V brake → R1/R7 divider → ~2.16 V @12V
 * Threshold at ~1.0 V: count = 1.0/3.3 × 4096 ≈ 1241                                  */
#define CFG_ADC_BRK_SOC      ADC_SOC_NUMBER1
#define CFG_ADC_BRK_CH       ADC_CH_ADCIN0
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#define CFG_PWM_MAX            4095U

/* ── CAN bus (CANA via WeAct CANFDSIO / IS2062A transceiver) ─────────────── */
/* GPIO31/30: avoids onboard SN65 on 32/33 when using external transceiver; free vs 4/5 enc/LEN */
#define CFG_CAN_TX_PIN         31U
#define CFG_CAN_TX_CONFIG      GPIO_31_CANA_TX
#define CFG_CAN_RX_PIN         30U
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#define CFG_CAN_RX_MAILBOX     1U
#define CFG_CAN_TX_MAILBOX     2U

/* Pin mux for CANA: 0=GPIO32/33 1=GPIO4/5 2=GPIO30/31 (recommended with external transceiver) */
#define CFG_CAN_PINMUX         2U

/* Application-level 11-bit CAN IDs */
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
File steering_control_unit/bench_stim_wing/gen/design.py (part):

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# (~39 V worst case). Everything on +12V is rated >= 40 V.
add("J2", "Connector_Generic:Conn_01x02", "12V IN",
    "Connector_JST:JST_PH_S2B-PH-K_1x02_P2.00mm_Horizontal",
    {"1": "V12_RAW", "2": "GND"}, note="JST PH 2-way, right angle. Pin 1 = +12 V", in_bom=False)
add("F1", "Device:Fuse", "2A", FUSE1206, {"1": "V12_RAW", "2": "V12_F"}, key="FUSE 2A",
    note="Input fuse, fast, 63 V")
DIODE("D1", "SS34", "V12_F", "+12V", "Diode_SMD:D_SMA", "Reverse-polarity protection", schottky=True)
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# Feed the Feather's USB pin (VBUS) through a Schottky: ~4.7 V there, below a
# PC's 5 V, so with a USB cable also plugged in the PC carries the load and this
# board never back-feeds the PC; the diode stops the PC feeding this board.
DIODE("D6", "PMEG6010CEH", "+5V", "VUSB", SOD123F, "5 V to the Feather USB pin, OR-ing diode", schottky=True)
C("C9", "100nF", "VUSB", "GND", "USB pin decoupling")

# --- SAS power (12 V, ~30 mA) -----------------------------------------------
# Q1 high side; Q2 pulls its gate. 10k/12k divider keeps Vgs <= 18 V at the TVS
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LEDIND("D7", "R10", "GRN", "SAS_12V", "SAS", r="10k")

# --- ARM loop (hard kill) ----------------------------------------------------
# +5V --F3--> J5 pin 7 ... external NC e-stop / key switch ... J5 pin 8 = ARM.
# ARM powers both relay coils and enables the IG1 output. Open loop: nothing
# can switch away from the car, whatever the firmware does.
add("F3", "Device:Polyfuse", "0.1A", FUSE1206, {"1": "+5V", "2": "ARM_SRC"}, key="PTC 0.1A",
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    NFET(q, en, "GND", low, ref + " coil driver")
    R(f"R{20 + 2 * i}", "100k", en, "GND", ref + " default off")
    DIODE(f"D{10 + 2 * i}", "1N4148WS", low, "ARM", SOD323, ref + " flyback")
    R(f"R{21 + 2 * i}", "1k", "ARM", f"LED_{label}", ref + " LED resistor")
    LED(f"D{11 + 2 * i}", "YEL", f"LED_{label}", low, ref + " energised")

# --- NEP / VSP outputs -------------------------------------------------------
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add("U4", "Interface_Expansion:TCA9534", "TCA9534", TSSOP16,
    dict(EXPANDER, **{"1": "GND", "2": "GND", "3": "GND", "8": "GND", "13": "EXP_INT",
                      "14": "SCL", "15": "SDA", "16": "+3V3"}),
    note="8-bit I2C GPIO, address 0x20. P0 SAS, P1 IG1, P2 K1, P3 K2 (outputs); P4 ARM, P5 12V (inputs)")
C("C13", "100nF", "+3V3", "GND", "U4 decoupling")
R("R35", "100k", "+12V", "V12_SENSE", "12 V sense divider, 14.4 V -> 3.6 V")
R("R36", "33k", "V12_SENSE", "GND", "12 V sense divider")
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# --- Connectors --------------------------------------------------------------
# J3, SAS + CAN pass-through (left end). Pins 3/5 and 4/6 are the same nets: one
# cable to the SAS, one pair on to the Feather M4 CAN terminal (X4: 1 L, 3 H).
J3_PINS = [("SAS_12V", "12V"), ("GND", "GND"), ("CANH", "CANH"), ("CANL", "CANL"),
           ("CANH", "H>FTH"), ("CANL", "L>FTH")]
# J4, torque sensor breakout (right end, top): GND between the two channels.
J4_PINS = [("VT3_EPS", "VT3 EPS"), ("VT3_CAR", "VT3 CAR"), ("GND", "GND"),
           ("VT6_EPS", "VT6 EPS"), ("VT6_CAR", "VT6 CAR")]
# J5, ECM signals + IG1 + ARM loop (right end, bottom). 12 V-level lines
# together (IG1, NEP), GND, then the 5 V-level lines (VSP, ARM loop).
J5_PINS = [("IG1_OUT", "IG1"), ("NEP_CAR", "NEP CAR"), ("NEP_EPS", "NEP EPS"), ("GND", "GND"),
           ("VSP_EPS", "VSP EPS"), ("VSP_CAR", "VSP CAR"), ("ARM_SRC", "ARM+"), ("ARM", "ARM")]
for ref, pins, val, note in [
        ("J3", J3_PINS, "SAS / CAN", "JST GH 6-way, right angle, locking"),
        ("J4", J4_PINS, "TORQUE", "JST GH 5-way, right angle, locking"),
        ("J5", J5_PINS, "ECM / IG1 / ARM", "JST GH 8-way, right angle, locking, back side")]:
    n = len(pins)
    nets = {str(i + 1): net for i, (net, _) in enumerate(pins)}
    nets["MP"] = "GND"
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
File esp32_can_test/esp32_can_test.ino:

/*
 * esp32_can_test.ino — ESP32 TWAI (CAN) TX/RX test
 *
 * Target hardware
 * ---------------
 * • ESP32 dev board, USB-C, CH340C USB–UART. Use the CH340 COM port at 115200 baud for
 *   Serial Monitor (this is unrelated to CAN bitrate).
 * • WeAct ISOCANFD Module V1 — CA-IS2062A, 2.5 kV isolated CAN/CAN-FD transceiver,
 *   logic I/O 2.5–5.5 V (3.3 V ESP32 is OK). The transceiver can do CAN FD; ESP32 TWAI
 *   here is classic CAN only (e.g. 500 kbps), which is fine for your throttle ECU bus.
 *
 * Wiring (follow WeAct silkscreen; names below are typical)
 * --------------------------------------------------------
 * Logic side → ESP32:
 *   3V3 / VCC → 3.3V
 *   GND       → GND
 *   Serial to/from ESP32 TWAI (Espressif-style pin choice):
 *     GPIO21 = TWAI TX (MCU out) → transceiver pin that accepts MCU transmit
 *     GPIO22 = TWAI RX (MCU in)  ← transceiver pin that drives MCU receive
 *   Some boards label these TXD/RXD from the transceiver’s point of view, which is the
 *   opposite of the MCU — if you get no RX/TX, swap GPIO21 and GPIO22 once.
 *
 * Isolated / bus side (per module datasheet):
 *   VBUS → 5 V (bus-side supply input where required)
 *   GNDB → isolated ground reference for CANH/CANL (not the same net as ESP32 GND)
 *   CANH / CANL → bus.
 *   IMPORTANT: With only this module on the bus, put ~120 Ω across CANH–CANL at the
 *   module. Floating lines cause bit errors → error passive → bus-off → TX returns 0x103
 *   (ESP_ERR_INVALID_STATE) until recovery finishes.
 *
 * TWAI mode vs F280049 on the same bus:
 *   NO_ACK helps solo bench TX but (on ESP-IDF) the node does not ACK other
 *   transmitters — the LAUNCHXL then gets ACK errors, bus-off, and RX/sniffer
 *   look dead. Use CAN_USE_NO_ACK_MODE 0 (NORMAL) with the C2000. Solo bench
 *   only: set CAN_USE_NO_ACK_MODE 1 and add ~120 Ω across CANH–CANL.
 *
 * 500 kbps; sniffer/TI/ESP32 must share one CANH/CANL pair + ground reference.
 */

#include <Arduino.h>
#include <string.h>
#include "driver/twai.h"
#include "esp_err.h"

static const char *twai_state_name(twai_state_t s)
{
    switch (s) {
    case TWAI_STATE_STOPPED:
        return "STOPPED";
    case TWAI_STATE_RUNNING:
        return "RUNNING";
    case TWAI_STATE_BUS_OFF:
        return "BUS_OFF";
    case TWAI_STATE_RECOVERING:
        return "RECOVERING";
    default:
        return "?";
    }
}

#define CAN_TX_PIN GPIO_NUM_21
#define CAN_RX_PIN GPIO_NUM_22

/* Must match all other devices on the bus (C2000 project uses 500000). */
#define CAN_BITRATE_KBPS 500

/* 0 = NORMAL — required with F280049 (or any peer) so you ACK their frames.
 * 1 = NO_ACK — solo bench only (see file header). */
#define CAN_USE_NO_ACK_MODE 0

#define TX_PERIOD_MS 500U

#define TX_CAN_ID 0x200U

static uint32_t txCount  = 0;
static uint32_t rxCount  = 0;
static uint16_t txCtr    = 0;
static uint32_t lastTxMs     = 0;
static uint32_t lastStateLog = 0;
static bool     driverOk     = false;

static bool installTwai(void)
{
    twai_mode_t mode = CAN_USE_NO_ACK_MODE ? TWAI_MODE_NO_ACK : TWAI_MODE_NORMAL;

    twai_general_config_t g_config =
        TWAI_GENERAL_CONFIG_DEFAULT(CAN_TX_PIN, CAN_RX_PIN, mode);

#if CAN_BITRATE_KBPS == 500
    twai_timing_config_t t_config = TWAI_TIMING_CONFIG_500KBITS();
#elif CAN_BITRATE_KBPS == 250
    twai_timing_config_t t_config = TWAI_TIMING_CONFIG_250KBITS();
#elif CAN_BITRATE_KBPS == 1000
    twai_timing_config_t t_config = TWAI_TIMING_CONFIG_1MBITS();
#else
#error Set CAN_BITRATE_KBPS to 250, 500, or 1000
#endif

    twai_filter_config_t f_config = TWAI_FILTER_CONFIG_ACCEPT_ALL();

    if (twai_driver_install(&g_config, &t_config, &f_config) != ESP_OK) {
        Serial.println("[CAN] ERROR: twai_driver_install failed");
        return false;
    }
    if (twai_start() != ESP_OK) {
        Serial.println("[CAN] ERROR: twai_start failed");
        twai_driver_uninstall();
        return false;
    }

    /* Older Arduino-ESP32 cores lack TWAI_ALERT_RECOVERY_COMPLETE; RUNNING is polled before TX. */
    uint32_t alerts = TWAI_ALERT_BUS_OFF | TWAI_ALERT_ERR_PASS |
                      TWAI_ALERT_BUS_ERROR | TWAI_ALERT_RX_DATA |
                      TWAI_ALERT_RX_QUEUE_FULL;
    if (twai_reconfigure_alerts(alerts, NULL) != ESP_OK) {
        Serial.println("[CAN] WARN: twai_reconfigure_alerts failed (continuing)");
    }

    return true;
}

static void handleAlerts(void)
{
    uint32_t alerts = 0;
    if (twai_read_alerts(&alerts, 0) != ESP_OK) {
        return;
    }

    if (alerts & TWAI_ALERT_BUS_OFF) {
        Serial.println("[CAN] Bus-off — twai_initiate_recovery() (no TX until RUNNING)");
        twai_initiate_recovery();
    }
    if (alerts & TWAI_ALERT_ERR_PASS) {
        Serial.println("[CAN] Alert: error passive (check 120R on CANH-CANL, wiring)");
    }
    if (alerts & TWAI_ALERT_BUS_ERROR) {
        twai_status_info_t st;
        if (twai_get_status_info(&st) == ESP_OK) {
            Serial.printf("[CAN] Bus error (count=%lu)\n",
                          (unsigned long)st.bus_error_count);
        }
    }
    if (alerts & TWAI_ALERT_RX_QUEUE_FULL) {
        Serial.println("[CAN] RX queue full — draining");
    }
}

void setup()
{
    Serial.begin(115200);
    delay(300);

    Serial.printf("[CAN] TWAI init: %u kbps, mode=%s\n",
                  (unsigned)CAN_BITRATE_KBPS,
                  CAN_USE_NO_ACK_MODE ? "NO_ACK (no peer ACK required)" : "NORMAL");

    driverOk = installTwai();
    if (!driverOk) {
        return;
    }

    lastTxMs = millis();
    Serial.printf("[CAN] Ready — TX id=0x%03X every %u ms, RX any\n",
                  (unsigned)TX_CAN_ID, (unsigned)TX_PERIOD_MS);
    Serial.println("[CAN] Tip: single-node bench needs ~120 Ohm between CANH and CANL.");
}

void loop()
{
    if (!driverOk) {
        delay(1000);
        return;
    }

    handleAlerts();

    twai_message_t rx;
    while (twai_receive(&rx, 0) == ESP_OK) {
        rxCount++;
        Serial.printf("[RX] #%lu  id=0x%03X  dlc=%u  %02X %02X %02X %02X %02X %02X %02X %02X\n",
                      (unsigned long)rxCount,
                      (unsigned)rx.identifier,
                      (unsigned)rx.data_length_code,
                      rx.data[0], rx.data[1], rx.data[2], rx.data[3],
                      rx.data[4], rx.data[5], rx.data[6], rx.data[7]);
    }

    uint32_t now = millis();
    if ((uint32_t)(now - lastTxMs) < TX_PERIOD_MS) {
        delay(1);
        return;
    }

    twai_status_info_t bus;
    if (twai_get_status_info(&bus) != ESP_OK) {
        delay(1);
        return;
    }

    /* twai_transmit returns ESP_ERR_INVALID_STATE (0x103) if not RUNNING (e.g. bus-off / recovering). */
    if (bus.state != TWAI_STATE_RUNNING) {
        if ((uint32_t)(now - lastStateLog) >= 2000U) {
            lastStateLog = now;
            Serial.printf("[CAN] TX held: state=%s — need RUNNING to transmit\n",
                          twai_state_name(bus.state));
            Serial.println("      Fix: ~120 Ohm between CANH & CANL (bench), bitrate, GPIO21/22 swap.");
            if (bus.state == TWAI_STATE_BUS_OFF) {
                twai_initiate_recovery();
            }
        }
        lastTxMs = now;
        delay(1);
        return;
    }

    lastTxMs = now;

    twai_message_t tx;
    memset(&tx, 0, sizeof(tx));
    tx.identifier       = TX_CAN_ID;
    tx.extd             = 0;
    tx.data_length_code = 4;
    tx.data[0]          = 0xBE;
    tx.data[1]          = 0xEF;
    tx.data[2]          = (uint8_t)(txCtr & 0xFF);
    tx.data[3]          = (uint8_t)((txCtr >> 8) & 0xFF);
    txCtr++;

    esp_err_t txErr = twai_transmit(&tx, pdMS_TO_TICKS(100));
    if (txErr == ESP_OK) {
        txCount++;
        Serial.printf("[TX] #%lu  id=0x%03X  %02X %02X %02X %02X\n",
                      (unsigned long)txCount,
                      (unsigned)tx.identifier,
                      tx.data[0], tx.data[1], tx.data[2], tx.data[3]);
    } else {
        Serial.printf("[TX] FAILED err=0x%X", (unsigned)txErr);
        if (txErr == ESP_ERR_INVALID_STATE) {
            Serial.print(" (INVALID_STATE: not RUNNING — bus-off/recovery/stopped)");
        }
        Serial.println();
        if (twai_get_status_info(&bus) == ESP_OK) {
            Serial.printf("      state=%s tx_fail=%lu bus_err=%lu\n",
                          twai_state_name(bus.state),
                          (unsigned long)bus.tx_failed_count,
                          (unsigned long)bus.bus_error_count);
        }
    }
}

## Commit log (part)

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2026-03-28 Release v1.0.0: C2000 CAN control, commander, ESP32 bench sketch
    - CAN 0x100 commands / 0x101 telemetry aligned with can_commander.py
    - can_io: CANA init, early RX, rate-limited TX; default pins GPIO31/30; 500 kbps
    - Safety: CAN heartbeat timeout and bus-off fault bits
    - Add esp32_can_test TWAI sketch for bench validation
    - throttle_gui: document CAN fault flags; root .gitignore for Python cache
    Made-with: Cursor
2026-04-09 updates
    not getting more detailed than that XD
